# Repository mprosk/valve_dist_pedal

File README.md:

# Valve Distortion Pedal
PCB for a Valvecaster style distortion pedal

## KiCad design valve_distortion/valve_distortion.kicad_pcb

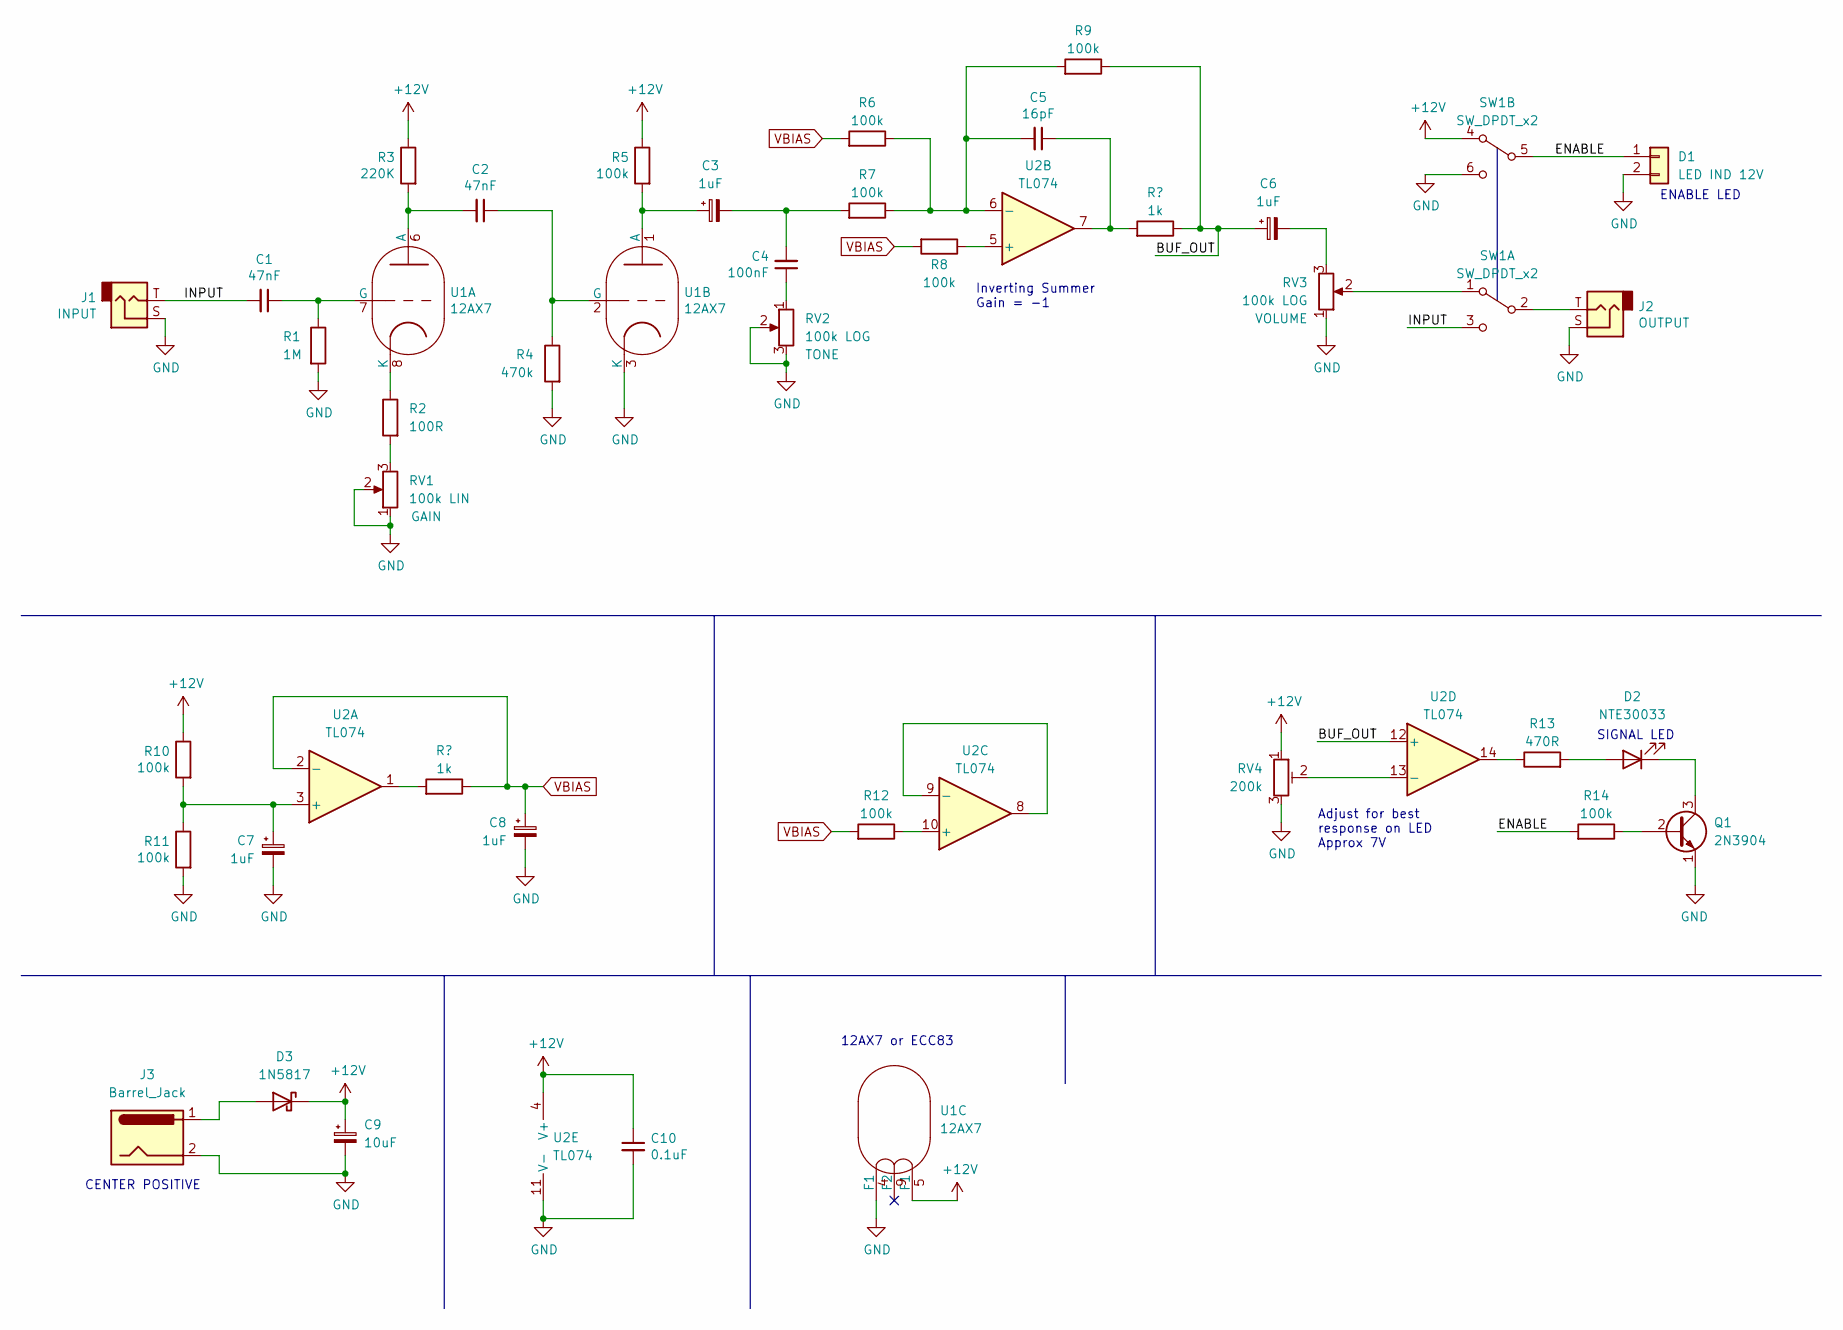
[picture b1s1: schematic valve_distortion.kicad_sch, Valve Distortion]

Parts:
C1, C2: 47nF; C_Disc_D4.3mm_W1.9mm_P5.00mm
C3, C6, C7, C8: 1uF; CP_Radial_D4.0mm_P2.00mm
C4: 100nF; C_Disc_D3.0mm_W1.6mm_P2.50mm
C5: 16pF; C_Disc_D3.0mm_W1.6mm_P2.50mm
C9: 10uF; CP_Radial_D5.0mm_P2.50mm
C10: 0.1uF; C_Disc_D3.0mm_W1.6mm_P2.50mm
D1: LED IND 12V; PinHeader_1x02_P2.54mm_Vertical
D2: NTE30033; PinHeader_1x02_P2.54mm_Vertical
D3: 1N5817; D_DO-41_SOD81_P10.16mm_Horizontal
J1: INPUT; PinHeader_1x02_P2.54mm_Vertical
J2: OUTPUT; PinHeader_1x02_P2.54mm_Vertical
J3: Barrel_Jack; Molex_KK-254_AE-6410-02A_1x02_P2.54mm_Vertical
Q1: 2N3904; TO-92_Inline
R1: 1M; R_Axial_DIN0207_L6.3mm_D2.5mm_P10.16mm_Horizontal
R2: 100R; R_Axial_DIN0207_L6.3mm_D2.5mm_P10.16mm_Horizontal
R3: 220K; R_Axial_DIN0207_L6.3mm_D2.5mm_P10.16mm_Horizontal
R4: 470k; R_Axial_DIN0207_L6.3mm_D2.5mm_P10.16mm_Horizontal
R5, R6, R7, R8, R9, R10, R11, R12, R14: 100k; R_Axial_DIN0207_L6.3mm_D2.5mm_P10.16mm_Horizontal
R13: 470R; R_Axial_DIN0207_L6.3mm_D2.5mm_P10.16mm_Horizontal
RV1: 100k LIN; Pot
RV2, RV3: 100k LOG; Pot
RV4: 200k; Trimmer
SW1: SW_DPDT_x2; PinHeader_2x03_P2.54mm_Vertical
U1: 12AX7; PinHeader_1x08_P2.54mm_Vertical
U2: TL074; DIP-14_W7.62mm

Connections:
+12V: C9.1, C10.1, D3.1 (K), R3.1, R5.1, R10.1, RV4.1, SW1.4 (A), U1.5 (F1), U2.4 (V+)
/ENABLE: D1.1, R14.2, SW1.5 (B)
/INPUT: C1.2, J1.T, SW1.3 (C)
GND: C7.2, C8.2, C9.2, C10.2, D1.2, J1.S, J2.S, J3.2, Q1.1 (E), R1.2, R4.2, R11.2, RV1.1, RV1.2, RV2.2, RV2.3, RV3.1, RV4.3, SW1.6 (C), U1.3 (K), U1.4 (F1), U2.11 (V-)
unnamed: C1.1, R1.1, U1.7 (G)
unnamed: C2.1, R4.1, U1.2 (G)
unnamed: C2.2, R3.2, U1.6 (A)
unnamed: C3.1, R5.2, U1.1 (A)
unnamed: C3.2, C4.2, R7.2
unnamed: C4.1, RV2.1
unnamed: C5.2, R6.1, R7.1, R9.2, U2.6 (-)
unnamed: C6.2, RV3.3
unnamed: C7.1, R10.2, R11.1, U2.3 (+)
unnamed: D2.1 (K), Q1.3 (C)
unnamed: D2.2 (A), R13.2
unnamed: D3.2 (A), J3.1
unnamed: J2.T, SW1.2 (B)
unnamed: Q1.2 (B), R14.1
unnamed: R2.1, U1.8 (K)
unnamed: R2.2, RV1.3
unnamed: R13.1, U2.14
unnamed: RV3.2, SW1.1 (A)
unnamed: RV4.2, U2.13 (-)
unnamed: R8.1, U2.5 (+)
unnamed: U2.8, U2.9 (-)
unnamed: R12.1, U2.10 (+)
VBIAS: C8.1, R6.2, R8.2, R12.2, U2.1, U2.2 (-)

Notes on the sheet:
12AX7 or ECC83
CENTER POSITIVE
Adjust for best response on LED Approx 7V
ENABLE LED
SIGNAL LED
Inverting Summer Gain = -1

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
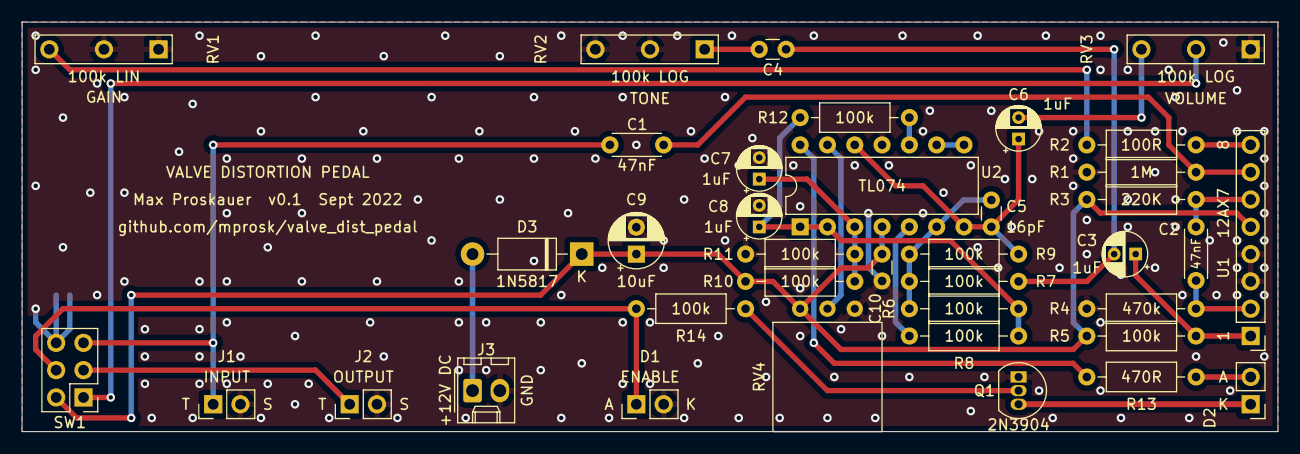
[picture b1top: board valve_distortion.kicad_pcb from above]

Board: 2 copper layers, 116.8 x 38.1 mm, 38 parts (0 on the bottom side), 28 nets.

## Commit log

2022-09-15 Initial commit from local
2022-09-20 Finish layout
2022-09-21 Include changes from scehmatic review
2022-09-25 Address opamp cap load
